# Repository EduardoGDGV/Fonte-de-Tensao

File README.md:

# Fonte de Tensão
Fonte de Tensão projetada para a matéria de Eletrônica para Computação, gerida por Eduardo do Valle Simões.
(USP_ICMC_Bacharelado em Ciências da Computação)

## Objetivo
Simular uma fonte capaz de transformar a tensão (127V - 220V) para utilização de 3V a 12V, sendo a corrente máxima de 100mA.

## Lista de Componentes
|   Componente   | Informações |  Preço   |
|----------------|-------------|----------|
|  [Transformador](https://www.baudaeletronica.com.br/transformador-trafo-12v-12v-500ma-110-220vac.html) |  12V 500mA  | R$ 22,23 |
|    [Diodo(4)](https://www.baudaeletronica.com.br/diodo-1n4007.html)    |   100V 1A   |  R$ 0,4  |
|    [Capacitor](https://www.baudaeletronica.com.br/capacitor-eletrolitico-470uf-25v.html)   |  470uF 25V  |  R$ 0,3  |
|  [Resistor 1K2](https://www.baudaeletronica.com.br/resistor-1k2-5-1-4w.html)  |   1K2 1/4W  |  R$ 0,07 |
|  [Resistor 5K6](https://www.baudaeletronica.com.br/resistor-5k6-5-1-4w.html)  |   5K6 1/4W  |  R$ 0,07 |
|  [Diodo Zener](https://www.baudaeletronica.com.br/diodo-zener-zmm-13v-0-5w.html)   |   13V 0,5W  |  R$ 0,13 |
|  [Potenciômetro](https://www.baudaeletronica.com.br/potenciometro-linear-de-10k-10000.html) |   10K 0,2W  |  R$ 1,32 |
|   [Transistor](https://www.baudaeletronica.com.br/transistor-npn-2n4401.html)   |    600mA    |  R$ 0,16 |
|                |             | R$ 24,68 |

## Simulação Falstad

## Simulação EAGLE

## Links e Créditos
1. Simulação Falstad: http://tinyurl.com/ybb3d6c8
2. Vídeo Explicativo: https://www.youtube.com/watch?v=v1oGl6g5wH8&feature=youtu.be
3. Eduardo Garcia de Gáspari Valdejão -> N°USP: 11795676

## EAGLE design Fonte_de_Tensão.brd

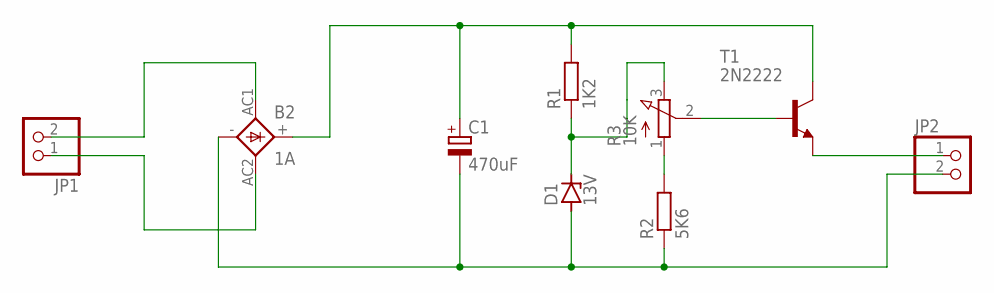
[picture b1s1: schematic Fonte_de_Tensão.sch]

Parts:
B2: 1A; GBPC1
C1: 470uF; E3,5-10
D1: 13V; DO35Z10
JP1, JP2: PINHD-1X2; 1X02
R1: 1K2; 0309/12
R2: 5K6; 0309/12
R3: 10K; 3RP/1610N
T1: 2N2222; TO18

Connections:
unnamed: B2.AC1, JP1.2
unnamed: B2.AC2, JP1.1
unnamed: B2.+, C1.+, R1.2, T1.3 (C)
unnamed: B2.-, C1.-, D1.A, JP2.2, R2.1
unnamed: JP2.1, T1.1 (E)
unnamed: R3.2 (S), T1.2 (B)
unnamed: R2.2, R3.1 (A)
unnamed: D1.C, R1.1, R3.3 (E)

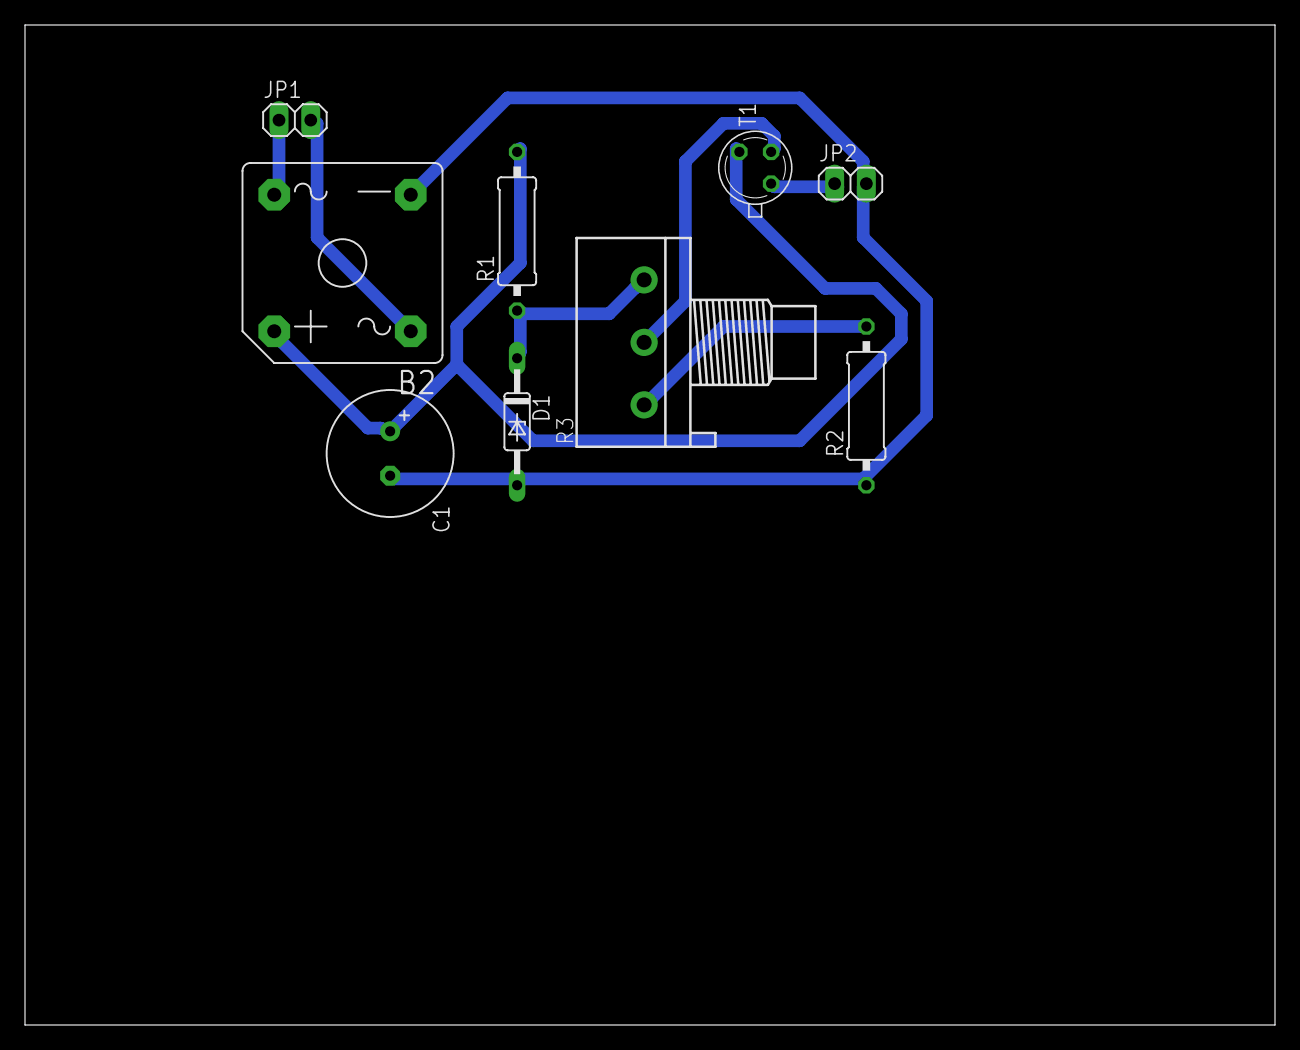
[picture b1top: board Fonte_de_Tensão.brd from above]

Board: 2 copper layers, 100.0 x 80.0 mm, 9 parts (0 on the bottom side), 8 nets.
